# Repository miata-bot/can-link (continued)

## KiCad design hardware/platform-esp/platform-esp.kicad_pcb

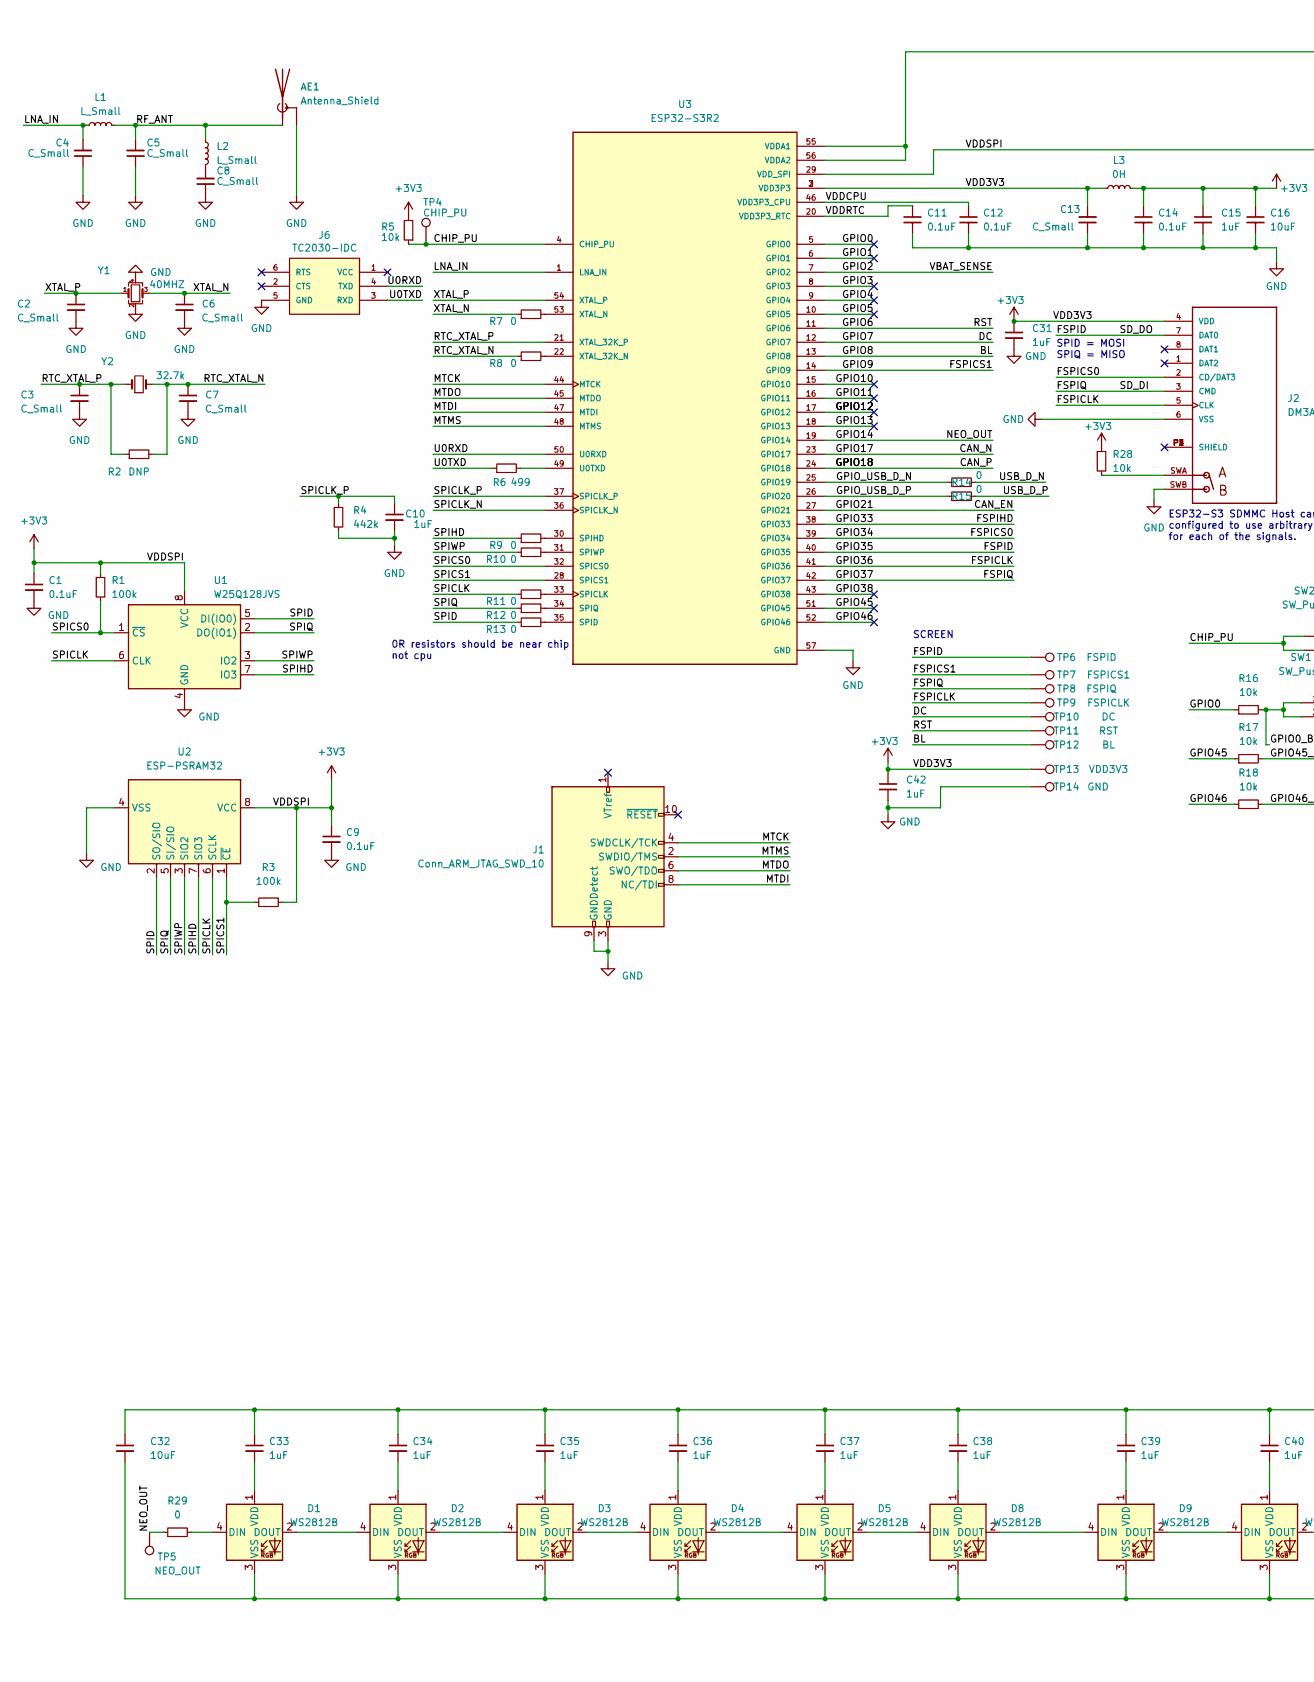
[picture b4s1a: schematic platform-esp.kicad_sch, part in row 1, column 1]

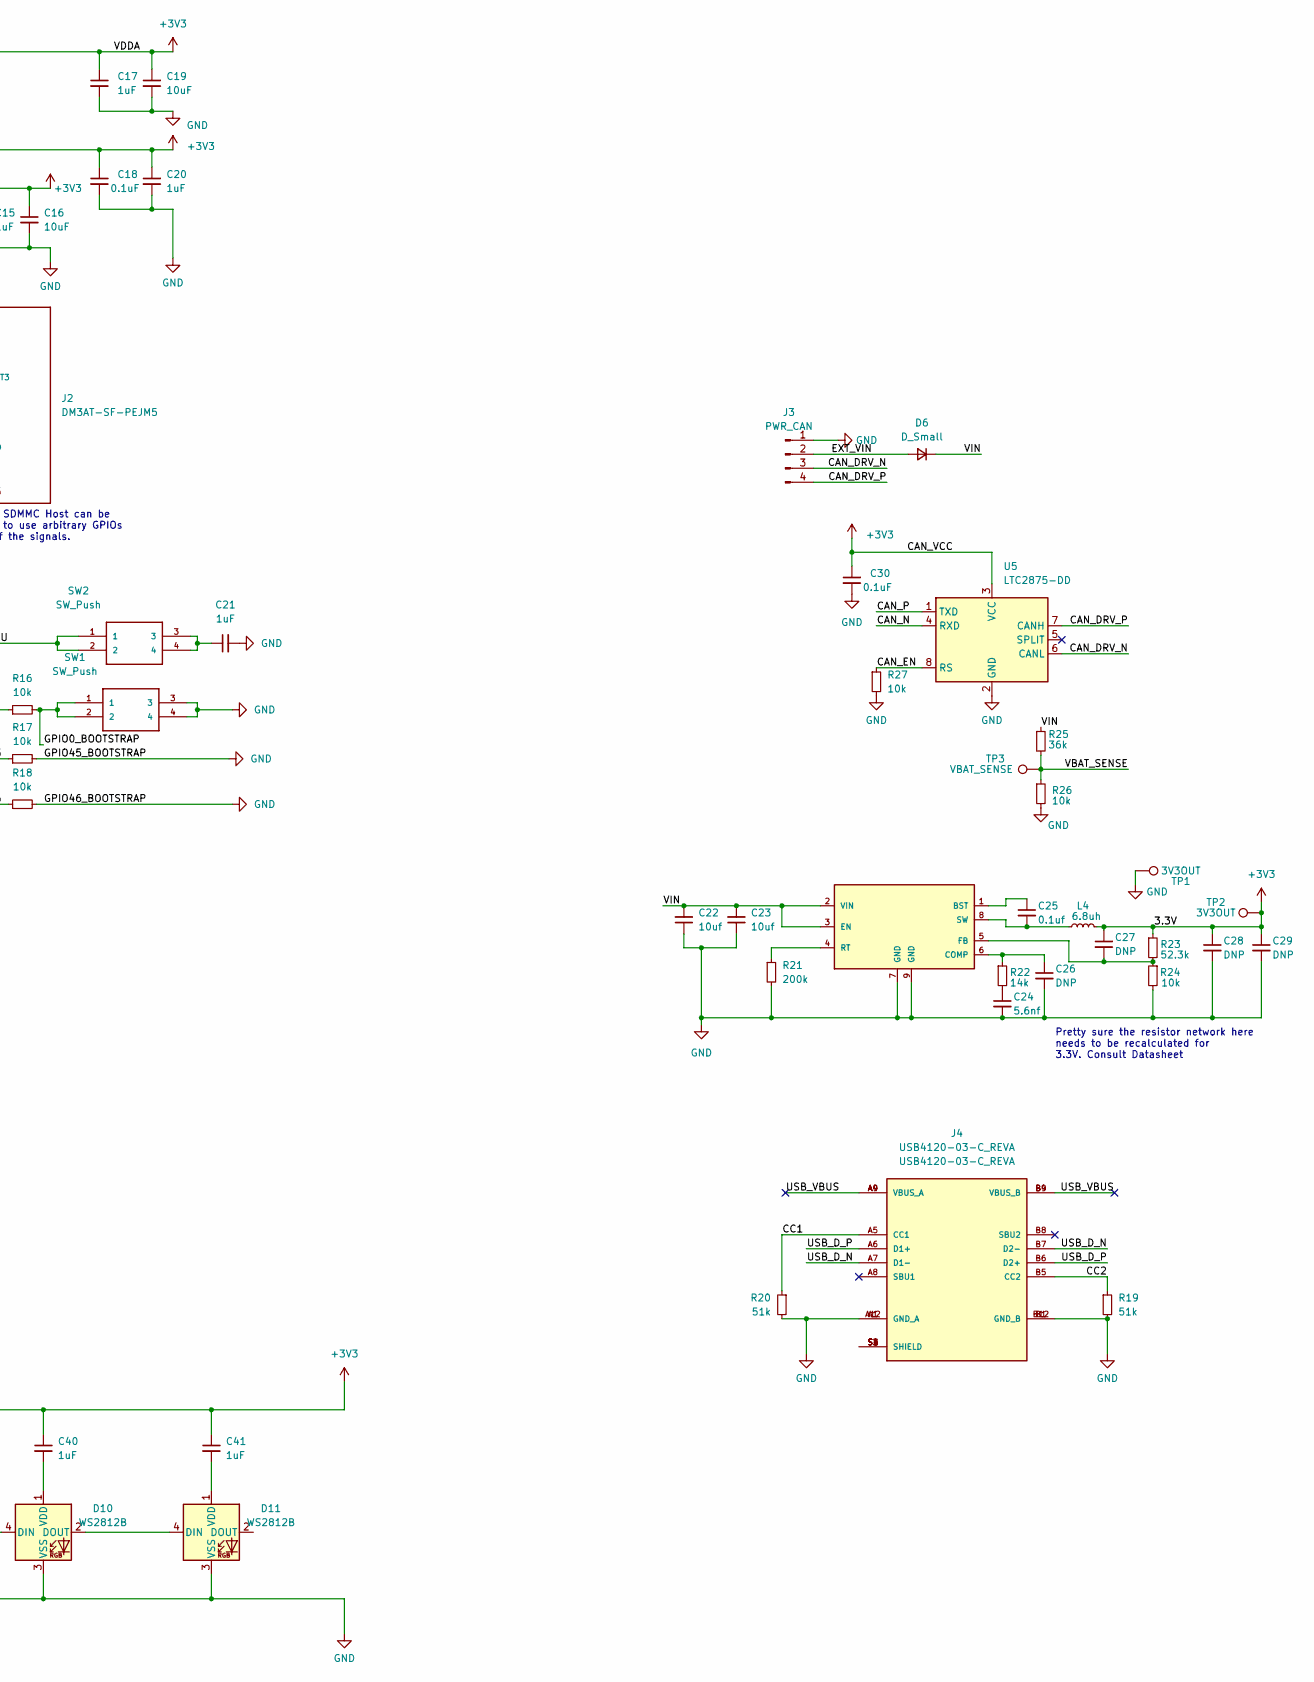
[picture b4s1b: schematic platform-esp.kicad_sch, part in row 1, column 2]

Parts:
AE1: Antenna_Shield; Texas_SWRA117D_2.4GHz_Left
C1, C9, C11, C12, C14, C18, C30: 0.1uF; C_0402_1005Metric
C2, C3, C4, C5, C6, C7, C8, C13: C_Small; C_0402_1005Metric
C10, C15, C17, C20, C21, C31, C33, C34, C35, C36, C37, C38, C39, C40, C41, C42: 1uF; C_0402_1005Metric
C16, C19, C32: 10uF; C_0402_1005Metric
C22, C23: 10uf; C_0805_2012Metric_Pad1.18x1.45mm_HandSolder; MPN C0805C106M3PAC7800
C24: 5.6nf; C_1206_3216Metric; MPN C1206C562KDRACAUTO
C25: 0.1uf; C_0805_2012Metric_Pad1.18x1.45mm_HandSolder; MPN 0805 (2012 Metric) 0,94mm
C26, C27, C28, C29: DNP; C_0805_2012Metric_Pad1.18x1.45mm_HandSolder
D1, D2, D3, D4, D5, D8, D9, D10, D11: WS2812B; LED_WS2812B_PLCC4_5.0x5.0mm_P3.2mm
D6: D_Small; D_SOD-123F
J1: Conn_ARM_JTAG_SWD_10; Tag-Connect_TC2050-IDC-NL_2x05_P1.27mm_Vertical
J2: DM3AT-SF-PEJM5; HRS_DM3AT-SF-PEJM5; MPN DM3AT-SF-PEJM5
J3: PWR_CAN; JST_GH_BM04B-GHS-TBT_1x04-1MP_P1.25mm_Vertical
J4: USB4120-03-C_REVA; GCT_USB4120-03-C_REVA; MPN USB4120-03-C_REVA
J6: TC2030-IDC; Tag-Connect_TC2030-IDC-NL_2x03_P1.27mm_Vertical
L1, L2: L_Small; L_0402_1005Metric
L3: 0H; L_0402_1005Metric
L4: 6.8uh; L_Bourns-SRN6028; MPN SRN6028-6R8M
R1, R3: 100k; R_0402_1005Metric
R2: DNP; R_0402_1005Metric
R4: 442k; R_0402_1005Metric
R5, R16, R17, R18, R26, R27, R28: 10k; R_0402_1005Metric
R6: 499; R_0402_1005Metric
R7, R8, R9, R10, R11, R12, R13, R14, R15, R29: 0; R_0402_1005Metric
R19, R20: 51k; R_0402_1005Metric
R21: 200k; R_0603_1608Metric_Pad0.98x0.95mm_HandSolder; MPN RMCF0603JT200K
R22: 14k; R_0603_1608Metric_Pad0.98x0.95mm_HandSolder; MPN RMCF0603FT14K0
R23: 52.3k; R_0603_1608Metric_Pad0.98x0.95mm_HandSolder; MPN RMCF0603FT52K3
R24: 10k; R_0603_1608Metric_Pad0.98x0.95mm_HandSolder; MPN RMCF0603JT10K0
R25: 36k; R_0402_1005Metric
SW1, SW2: SW_Push; PTS810SJG250SMTRLFS; MPN PTS810SJK250SMTRLFS
TP1, TP2: 3V3OUT; TestPoint_Pad_D1.0mm
TP3: VBAT_SENSE; TestPoint_Pad_D1.0mm
TP4: CHIP_PU; TestPoint_Pad_D1.0mm
TP5: NEO_OUT; TestPoint_Pad_D1.0mm
TP6: FSPID; TestPoint_Pad_D1.0mm
TP7: FSPICS1; TestPoint_Pad_D1.0mm
TP8: FSPIQ; TestPoint_Pad_D1.0mm
TP9: FSPICLK; TestPoint_Pad_D1.0mm
TP10: DC; TestPoint_Pad_D1.0mm
TP11: RST; TestPoint_Pad_D1.0mm
TP12: BL; TestPoint_Pad_D1.0mm
TP13: VDD3V3; TestPoint_Pad_D1.0mm
TP14: GND; TestPoint_Pad_D1.0mm
U1: W25Q128JVS; SOIC-8_5.23x5.23mm_P1.27mm
U2: ESP-PSRAM32; SOIC-8_3.9x4.9mm_P1.27mm
U3: ESP32-S3R2; QFN-56-1EP_7x7mm_P0.4mm_EP5.6x5.6mm
U4: AP64200Q; SOIC-8-1EP_3.9x4.9mm_P1.27mm_EP2.29x3mm_ThermalVias; MPN AP64200QSP-13
U5: LTC2875-DD; DFN-8-1EP_3x3mm_P0.5mm_EP1.66x2.38mm
Y1: 40MHZ; Crystal_SMD_2016-4Pin_2.0x1.6mm; MPN ECS-400-10-37B2-CKY-TR
Y2: 32.7k; Crystal_SMD_MicroCrystal_CC7V-T1A-2Pin_3.2x1.5mm

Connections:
+3V3: C1.1, C9.1, C13.2, C14.1, C15.1, C16.1, C17.1, C18.1, C19.1, C20.1, C27.1, C28.1, C29.1, C30.1, C31.1, C32.1, C33.1, C34.1, C35.1, C36.1, C37.1, C38.1, C39.1, C40.1, C41.1, C42.1, J2.4 (VDD), L3.1, L3.2, L4.2, R1.1, R3.2, R5.2, R23.1, R28.1, TP2.1, TP13.1, U1.8 (VCC), U2.8 (VCC), U3.2 (VDD3P3), U3.3 (VDD3P3), U3.29 (VDD_SPI), U3.55 (VDDA1), U3.56 (VDDA2), U5.3 (VCC)
/CAN_DRV_N: J3.3, U5.6 (CANL)
/CAN_DRV_P: J3.4, U5.7 (CANH)
/CAN_EN: R27.1, U3.27 (GPIO21), U5.8 (RS)
/CAN_N: U3.23 (GPIO17), U5.4 (RXD)
/CAN_P: U3.24 (GPIO18), U5.1 (TXD)
/CC1: J4.A5 (CC1), R20.1
/CC2: J4.B5 (CC2), R19.1
/CHIP_PU: R5.1, SW2.1, SW2.2, TP4.1, U3.4 (CHIP_PU)
/DC: TP10.1, U3.12 (GPIO7)
/EXT_VIN: D6.2 (A), J3.2
/FSPICLK: J2.5 (CLK), TP9.1, U3.41 (GPIO36)
/FSPICS0: J2.2 (CD/DAT3), U3.39 (GPIO34)
/FSPID: J2.7 (DAT0), TP6.1, U3.40 (GPIO35)
/FSPIHD: U3.38 (GPIO33)
/FSPIQ: J2.3 (CMD), TP8.1, U3.42 (GPIO37)
/GPIO0: R16.1, U3.5 (GPIO0)
/GPIO0_BOOTSTRAP: R16.2, SW1.1, SW1.2
/GPIO1: U3.6 (GPIO1)
/GPIO2: R25.2, R26.1, TP3.1, U3.7 (GPIO2)
/GPIO3: U3.8 (GPIO3)
/GPIO4: U3.9 (GPIO4)
/GPIO5: U3.10 (GPIO5)
/GPIO6: TP11.1, U3.11 (GPIO6)
/GPIO8: TP12.1, U3.13 (GPIO8)
/GPIO9: TP7.1, U3.14 (GPIO9)
/GPIO10: U3.15 (GPIO10)
/GPIO11: U3.16 (GPIO11)
/GPIO12: U3.17 (GPIO12)
/GPIO13: U3.18 (GPIO13)
/GPIO14: R29.1, TP5.1, U3.19 (GPIO14)
/GPIO38: U3.43 (GPIO38)
/GPIO45: R17.1, U3.51 (GPIO45)
/GPIO46: R18.1, U3.52 (GPIO46)
/GPIO_USB_D_N: R14.1, U3.25 (GPIO19)
/GPIO_USB_D_P: R15.1, U3.26 (GPIO20)
/LNA_IN: C4.2, L1.1, U3.1 (LNA_IN)
/MTCK: J1.4 (SWDCLK/TCK), U3.44 (MTCK)
/MTDI: J1.8 (NC/TDI), U3.47 (MTDI)
/MTDO: J1.6 (SWO/TDO), U3.45 (MTDO)
/MTMS: J1.2 (SWDIO/TMS), U3.48 (MTMS)
/RF_ANT: AE1.1 (A), C5.2, L1.2, L2.1
/RTC_XTAL_N: C7.1, R2.2, R8.1, Y2.2
/RTC_XTAL_P: C3.1, R2.1, U3.21 (XTAL_32K_P), Y2.1
/SPICLK: R11.1, U1.6 (CLK), U2.6 (SCLK)
/SPICLK_N: U3.36 (SPICLK_N)
/SPICLK_P: C10.1, R4.1, U3.37 (SPICLK_P)
/SPICS0: R1.2, U1.1 (~CS), U3.32 (SPICS0)
/SPICS1: R3.1, U2.1 (~CE), U3.28 (SPICS1)
/SPID: R13.1, U1.5 (DI(IO0)), U2.2 (SO/SIO)
/SPIHD: R9.1, U1.7 (IO3), U2.7 (SIO3)
/SPIQ: R12.1, U1.2 (DO(IO1)), U2.5 (SI/SIO)
/SPIWP: R10.1, U1.3 (IO2), U2.3 (SIO2)
/U0RXD: J6.4 (TXD), U3.50 (U0RXD)
/U0TXD: J6.3 (RXD), R6.1
/USB_D_N: J4.A7 (D1-), J4.B7 (D2-), R14.2
/USB_D_P: J4.A6 (D1+), J4.B6 (D2+), R15.2
/USB_VBUS: J4.A4 (VBUS_A), J4.A9 (VBUS_A), J4.B4 (VBUS_B), J4.B9 (VBUS_B)
/VDDCPU: C12.1, U3.46 (VDD3P3_CPU)
/VDDRTC: C11.1, U3.20 (VDD3P3_RTC)
/VIN: C22.2, C23.2, D6.1 (K), R25.1, U4.2 (VIN), U4.3 (EN)
/XTAL_N: C6.1, R7.1, Y1.3
/XTAL_P: C2.1, U3.54 (XTAL_P), Y1.1
GND: AE1.2 (Shield), C1.2, C2.2, C3.2, C4.1, C5.1, C6.2, C7.2, C8.1, C9.2, C10.2, C11.2, C12.2, C13.1, C14.2, C15.2, C16.2, C17.2, C18.2, C19.2, C20.2, C21.2, C22.1, C23.1, C24.2, C26.2, C28.2, C29.2, C30.2, C31.2, C32.2, C42.2, D1.3 (VSS), D2.3 (VSS), D3.3 (VSS), D4.3 (VSS), D5.3 (VSS), D8.3 (VSS), D9.3 (VSS), D10.3 (VSS), D11.3 (VSS), J1.3 (GND), J1.5 (GND), J1.9 (GNDDetect), J2.6 (VSS), J2.SWB, J3.1, J4.A1 (GND_A), J4.A12 (GND_A), J4.B1 (GND_B), J4.B12 (GND_B), J6.5 (GND), R4.2, R17.2, R18.2, R19.2, R20.2, R21.2, R24.2, R26.2, R27.2, SW1.3, SW1.4, TP1.1, TP14.1, U1.4 (GND), U2.4 (VSS), U3.57 (GND), U4.7 (GND), U4.9 (GND), U5.2 (GND), U5.9 (GND), Y1.2, Y1.4
unnamed: C8.2, L2.2
unnamed: C21.1, SW2.3, SW2.4
unnamed: C24.1, R22.2
unnamed: C25.1, U4.1 (BST)
unnamed: C25.2, L4.1, U4.8 (SW)
unnamed: C26.1, R22.1, U4.6 (COMP)
unnamed: C27.2, R23.2, R24.1, U4.5 (FB)
unnamed: C33.2, D1.1 (VDD)
unnamed: C34.2, D2.1 (VDD)
unnamed: C35.2, D3.1 (VDD)
unnamed: C36.2, D4.1 (VDD)
unnamed: C37.2, D5.1 (VDD)
unnamed: C38.2, D8.1 (VDD)
unnamed: C39.2, D9.1 (VDD)
unnamed: C40.2, D10.1 (VDD)
unnamed: C41.2, D11.1 (VDD)
unnamed: D1.2 (DOUT), D2.4 (DIN)
unnamed: D1.4 (DIN), R29.2
unnamed: D2.2 (DOUT), D3.4 (DIN)
unnamed: D3.2 (DOUT), D4.4 (DIN)
unnamed: D4.2 (DOUT), D5.4 (DIN)
unnamed: D5.2 (DOUT), D8.4 (DIN)
unnamed: D8.2 (DOUT), D9.4 (DIN)
unnamed: D10.2 (DOUT), D11.4 (DIN)
unnamed: D9.2 (DOUT), D10.4 (DIN)
unnamed: J2.SWA, R28.2
unnamed: R6.2, U3.49 (U0TXD)
unnamed: R7.2, U3.53 (XTAL_N)
unnamed: R8.2, U3.22 (XTAL_32K_N)
unnamed: R9.2, U3.30 (SPIHD)
unnamed: R10.2, U3.31 (SPIWP)
unnamed: R11.2, U3.33 (SPICLK)
unnamed: R12.2, U3.34 (SPIQ)
unnamed: R13.2, U3.35 (SPID)
unnamed: R21.1, U4.4 (RT)

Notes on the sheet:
SCREEN
ESP32-S3 SDMMC Host can be configured to use arbitrary GPIOs for each of the signals.
SPID = MOSI SPIQ = MISO
0R resistors should be near chip not cpu
Pretty sure the resistor network here needs to be recalculated for 3.3V. Consult Datasheet

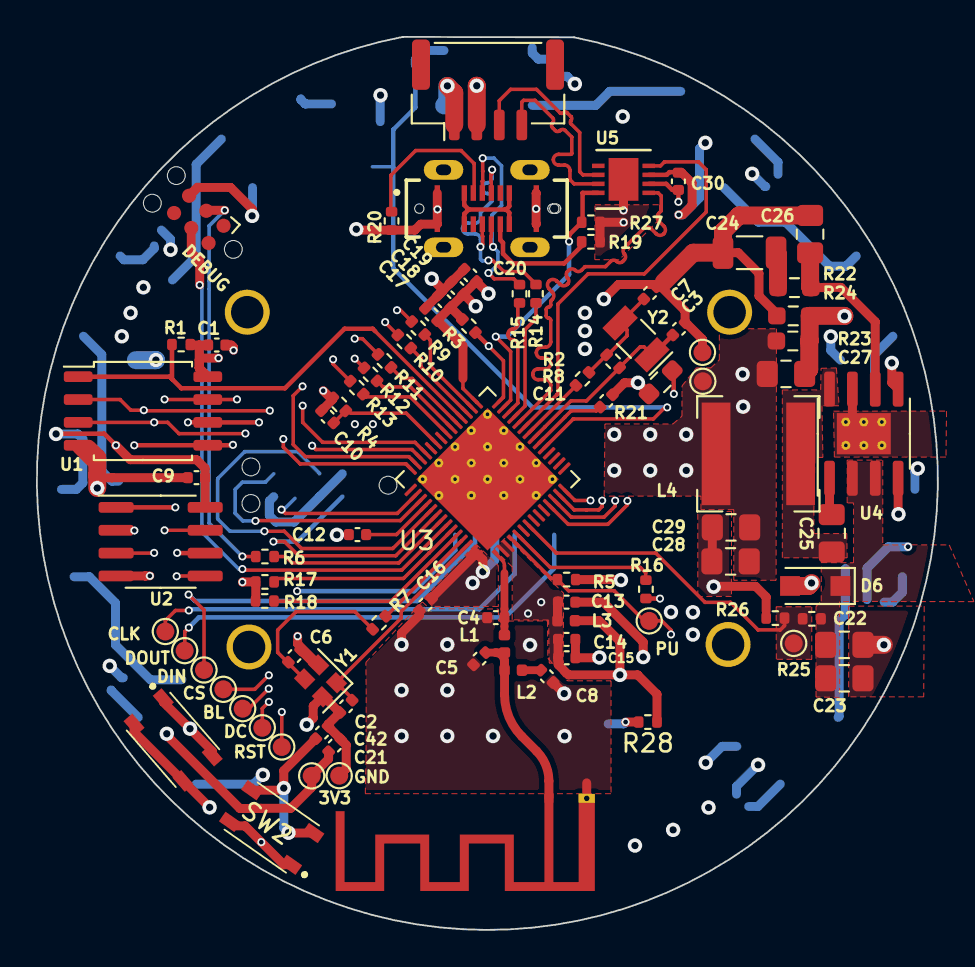
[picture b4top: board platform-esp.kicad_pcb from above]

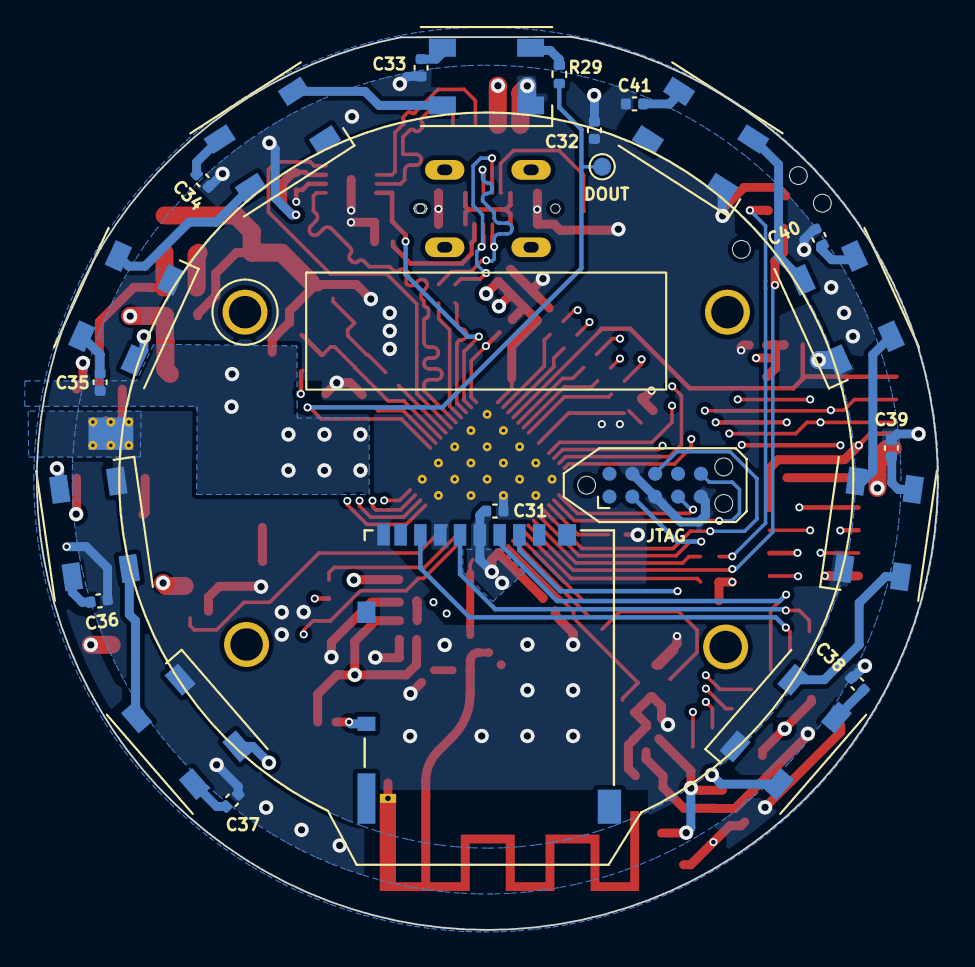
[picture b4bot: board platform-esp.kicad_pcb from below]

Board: 4 copper layers, 50.0 x 49.6 mm, 114 parts (24 on the bottom side), 88 nets.
